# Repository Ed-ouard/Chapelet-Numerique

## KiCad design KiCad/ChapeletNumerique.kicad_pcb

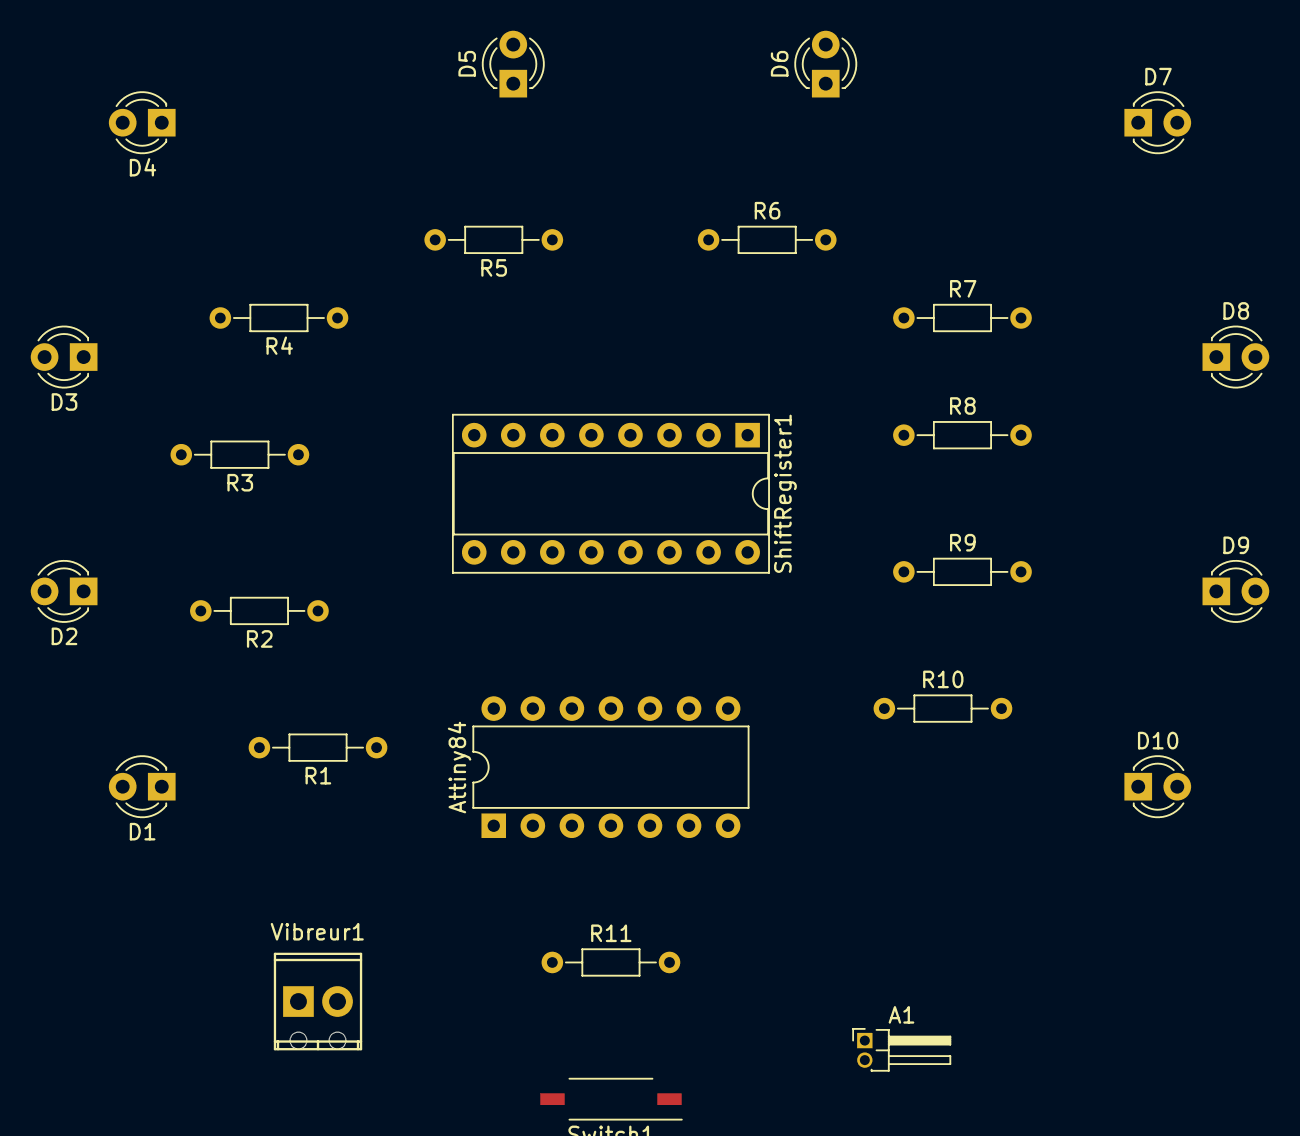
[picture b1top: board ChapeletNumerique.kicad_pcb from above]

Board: 2 copper layers, 26 parts (0 on the bottom side), 28 nets, no tracks yet.

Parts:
A1: Alimentation; Pin_Header_Angled_1x02_Pitch1.27mm
Attiny84: ATTINY84A-PU; DIP-14_W7.62mm
D1, D2, D3, D4, D5, D6, D7, D8, D9, D10: LED; LED_D3.0mm
R1, R2, R3, R4, R5, R6, R7, R8, R9, R10: 150; R_Axial_DIN0204_L3.6mm_D1.6mm_P7.62mm_Horizontal
R11: 1k; R_Axial_DIN0204_L3.6mm_D1.6mm_P7.62mm_Horizontal
ShiftRegister1: 74HC595; DIP-16_W7.62mm_Socket
Switch1: SW_DIP_x01; SW_DIP_x1_W7.62mm_Slide_Copal_CHS-B
Vibreur1: Motor_DC_ALT; TerminalBlock_Phoenix_MPT-2.54mm_2pol

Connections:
/switch: Attiny84.11, Switch1.1
GND: A1.1, Attiny84.14, D1.2, D2.2, D3.2, D4.2, D5.2, D6.2, D7.2, D8.2, D9.2, D10.2, R11.2, ShiftRegister1.8, ShiftRegister1.13, Vibreur1.1
unnamed: Attiny84.2, R10.1
unnamed: Attiny84.3, ShiftRegister1.10
unnamed: Attiny84.6, Vibreur1.2
unnamed: Attiny84.8, ShiftRegister1.14
unnamed: Attiny84.9, ShiftRegister1.12
unnamed: Attiny84.10, ShiftRegister1.11
unnamed: Attiny84.12, R9.1
unnamed: D1.1, R1.2
unnamed: D2.1, R2.2
unnamed: D3.1, R3.2
unnamed: D4.1, R4.2
unnamed: D5.1, R5.2
unnamed: D6.1, R6.2
unnamed: D7.1, R7.2
unnamed: D8.1, R8.2
unnamed: D9.1, R9.2
unnamed: D10.1, R10.2
unnamed: R1.1, ShiftRegister1.15
unnamed: R2.1, ShiftRegister1.1
unnamed: R3.1, ShiftRegister1.2
unnamed: R4.1, ShiftRegister1.3
unnamed: R5.1, ShiftRegister1.4
unnamed: R6.1, ShiftRegister1.5
unnamed: R7.1, ShiftRegister1.6
unnamed: R8.1, ShiftRegister1.7
VCC: A1.2, Attiny84.1, R11.1, ShiftRegister1.16, Switch1.2

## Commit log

2018-02-26 Creation
2018-02-26 Button + Buzzer + sequence
2018-02-26 feat(Fritzing) ajout des fichiers Fritzing
2018-02-26 feat(Fritzing) ajout du routage pour le schéma
2018-02-26 ATTiny84 version
2018-02-26 Update with working buzzer
2018-02-26 feat(img) modification de l'image Arduino
2018-02-26 feat(sch) Schematics Fritzing
2018-02-26 feat(Fritzing) Schematics finished.
2018-02-26 feat(Fritzing) Tiny breadboard and PNG image
2018-02-26 Leds order modified
    Leds indépendantes : 9 et 10
2018-02-27 feat(PCB) add PCB layout
2018-02-27 feat(PCB) PCB finished
2018-02-27 feat(PCB) rework the PCB and breadboard, all cables are OK
2018-02-27 feat(PCB) ready to print
2018-02-28 feat(PCB) update PCB schematics
2018-03-07 doc(Fritzing) create a Fritzing directory for all Fritzing files
2018-03-07 feat(KiCad) add KiCad files
2018-03-07 doc(img) rename image files
2018-03-14 feat(KiCad) finish schematics
2018-03-14 feat(kicad) add PCB schema
2018-03-14 fear(kicad) PCB finished
2018-03-14 feat(kicad) update schematic
